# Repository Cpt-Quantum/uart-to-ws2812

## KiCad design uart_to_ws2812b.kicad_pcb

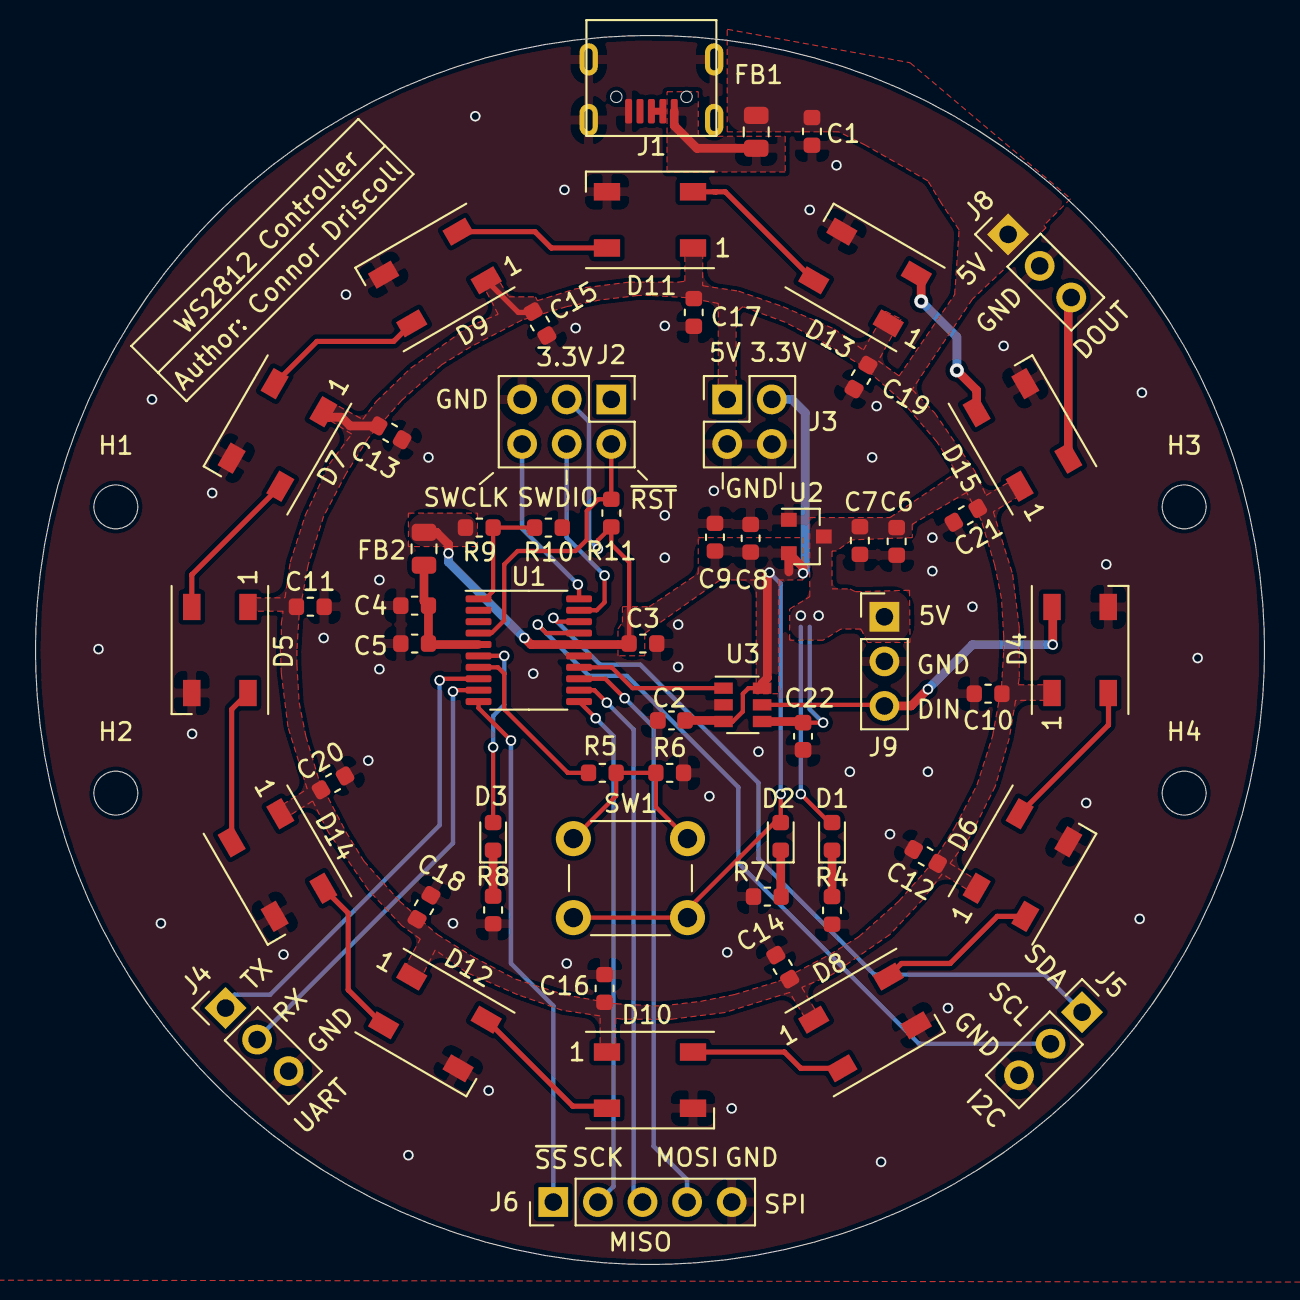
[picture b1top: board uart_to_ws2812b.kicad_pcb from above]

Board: 2 copper layers, 70.0 x 70.0 mm, 63 parts (0 on the bottom side), 38 nets.

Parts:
C1: 4.7uF; C_0603_1608Metric
C2, C3, C4, C10, C11, C12, C13, C14, C15, C16, C17, C18, C19, C20, C21, C22: 0.1uF; C_0603_1608Metric
C5, C7, C8: 10nF; C_0603_1608Metric
C6, C9: 1.0uF; C_0603_1608Metric
D1, D2, D3: LED; LED_0603_1608Metric
D4, D5, D6, D7, D8, D9, D10, D11, D12, D13, D14, D15: WS2812B; LED_WS2812B_PLCC4_5.0x5.0mm_P3.2mm
FB1, FB2: Ferrite_Bead; L_0805_2012Metric
H1, H2, H3, H4: MountingHole; MountingHole_2.5mm
J1: USB_B_Micro; USB-MicroB
J2: Prog. Header; PinHeader_2x03_P2.54mm_Vertical
J3: Power Header; PinHeader_2x02_P2.54mm_Vertical
J4: UART; PinHeader_1x03_P2.54mm_Vertical
J5: I2C; PinHeader_1x03_P2.54mm_Vertical
J6: SPI; PinHeader_1x05_P2.54mm_Vertical
J8, J9: Conn_01x03; PinHeader_1x03_P2.54mm_Vertical
R4: 600R; R_0603_1608Metric
R5, R6, R9, R10, R11: 10kR; R_0603_1608Metric
R7, R8: 260R; R_0603_1608Metric
SW1: SW_Push; SW_PUSH_6mm_H5mm
U1: STM32F030F4Px; TSSOP-20_4.4x6.5mm_P0.65mm
U2: SSP6206; SOT-23
U3: PI4ULS5V201TAEX; SOT-23-6

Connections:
+3V3: C2.1, C3.1, C8.1, C9.1, D2.2, FB2.2, J2.3, J3.2, R9.1, R11.1, SW1.2, U1.16, U2.2, U3.3, U3.6
+5V: C1.1, C6.1, C7.1, C10.1, C11.1, C12.1, C13.1, C14.1, C15.1, C16.1, C17.1, C18.1, C19.1, C20.1, C21.1, C22.1, D1.2, D4.1, D5.1, D6.1, D7.1, D8.1, D9.1, D10.1, D11.1, D12.1, D13.1, D14.1, D15.1, FB1.1, J3.1, J8.1, J9.1, U2.3, U3.4
/3.3V_Data_Out: U1.14, U3.1
/3.3V_LED_K: D2.1, R7.1
/5V_Data_Out: D4.4, J9.3, U3.5
/5V_LED_K: D1.1, R4.1
/Addressable_LEDs/DOUT_1: D4.2, D6.4
/Addressable_LEDs/DOUT_2: D6.2, D8.4
/Addressable_LEDs/DOUT_3: D8.2, D10.4
/Addressable_LEDs/DOUT_4: D10.2, D12.4
/Addressable_LEDs/DOUT_5: D12.2, D14.4
/Addressable_LEDs/DOUT_6: D5.4, D14.2
/Addressable_LEDs/DOUT_7: D5.2, D7.4
/Addressable_LEDs/DOUT_8: D7.2, D9.4
/Addressable_LEDs/DOUT_9: D9.2, D11.4
/Addressable_LEDs/DOUT_10: D11.2, D13.4
/Addressable_LEDs/DOUT_11: D13.2, D15.4
/DOUT: D15.2, J8.3
/I2C_SCL: J5.2, U1.17
/I2C_SDA: J5.1, U1.18
/PA0: D3.2, U1.6
/PA1: R5.2, U1.7
/SPI_MISO: J6.3, U1.12
/SPI_MOSI: J6.4, U1.13
/SPI_SCK: J6.2, U1.11
/SPI_~SS: J6.1, U1.10
/STM32F030F4Px/BOOT0: R9.2, R10.1, U1.1
/STM32F030F4Px/VDDA: C4.1, C5.1, FB2.1, U1.5
/SWCLK: J2.6, U1.20
/SWDIO: J2.4, U1.19
/UART_RX: J4.2, U1.9
/UART_TX: J4.1, U1.8
/User_LED_K: D3.1, R8.1
/V_USB: FB1.2, J1.1
/~RST: J2.2, R11.2, U1.4
GND: C1.2, C2.2, C3.2, C4.2, C5.2, C6.2, C7.2, C8.2, C9.2, C10.2, C11.2, C12.2, C13.2, C14.2, C15.2, C16.2, C17.2, C18.2, C19.2, C20.2, C21.2, C22.2, D4.3, D5.3, D6.3, D7.3, D8.3, D9.3, D10.3, D11.3, D12.3, D13.3, D14.3, D15.3, J1.5, J1.6, J2.5, J3.3, J3.4, J4.3, J5.3, J6.5, J8.2, J9.2, R4.2, R6.2, R7.2, R8.2, R10.2, U1.15, U2.1, U3.2
unnamed: J1.2, J1.3
unnamed: R5.1, R6.1, SW1.1

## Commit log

2020-09-09 Initial schematic/board file commit
2020-09-09 Added 3d render
2020-11-07 Updated copper pours to avoid short between V_USB and GND
2020-11-07 Fixed some minor silk screen bugs
2020-11-14 Shorted D+ and D- to indicate charging mode
2020-12-18 Added basic blinky firmware
2021-01-16 Changed to a level shifting IC for the LED data logic
2021-03-27 Updated component information with more detail
2021-03-27 Tweaked .gitignore
2021-03-27 Changed firmware to use ST device header, added WS2812 support
2021-03-27 Added basic logic to allow support for both RGB and RGBW LEDs
